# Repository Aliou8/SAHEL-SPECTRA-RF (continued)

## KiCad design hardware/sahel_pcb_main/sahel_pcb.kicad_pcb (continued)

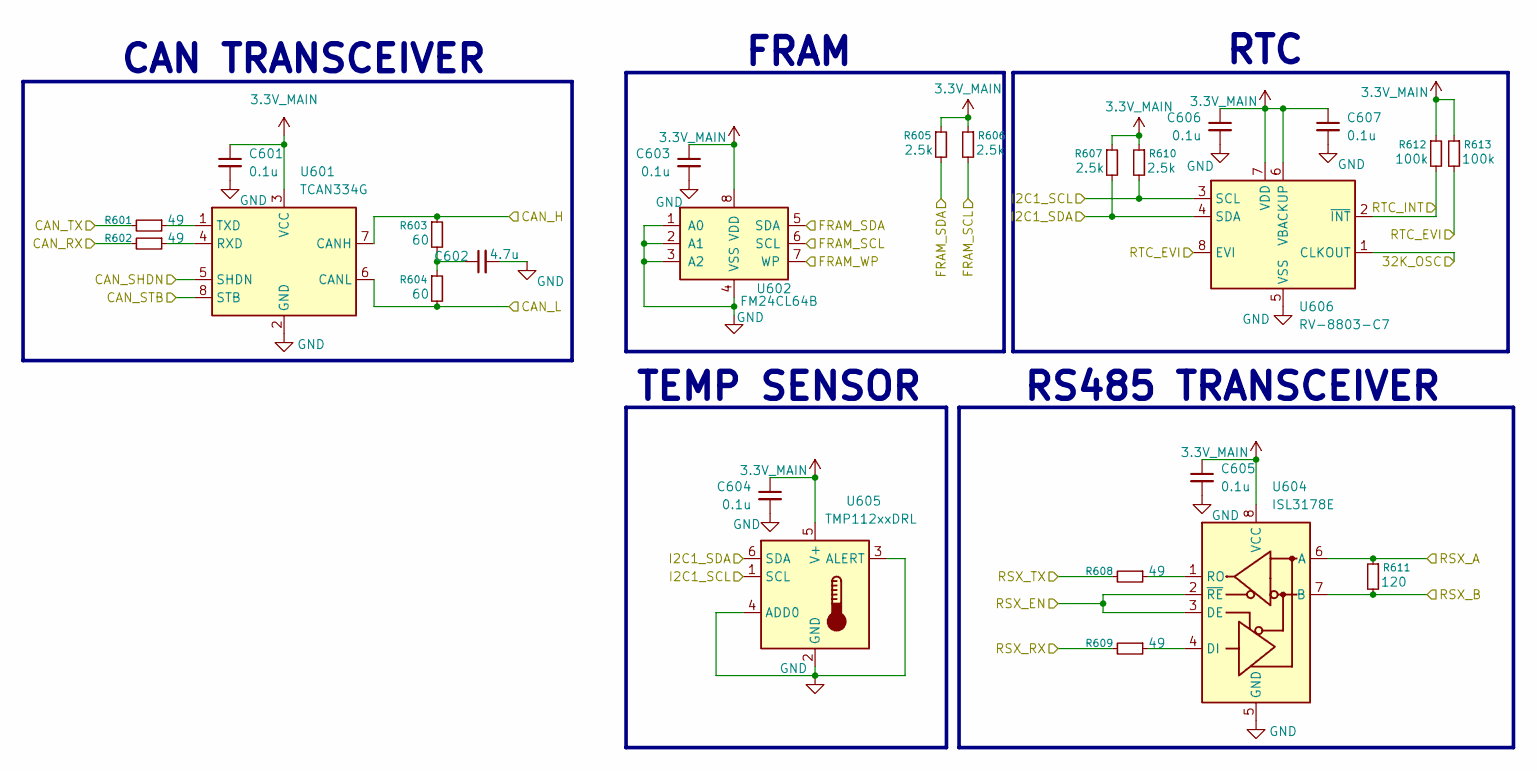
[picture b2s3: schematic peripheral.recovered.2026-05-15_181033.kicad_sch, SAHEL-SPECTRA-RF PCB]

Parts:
C601, C603, C604, C605, C606, C607: 0.1u; C_0402_1005Metric
C602: 4.7u; C_0402_1005Metric
R601, R602, R608, R609: 49; R_0402_1005Metric
R603, R604: 60; R_0402_1005Metric
R605, R606, R607, R610: 2.5k; R_0402_1005Metric
R611: 120; R_0402_1005Metric
R612, R613: 100k; R_0402_1005Metric
U601: TCAN334G; TSOT-23-8
U602: FM24CL64B; SOIC-8_3.9x4.9mm_P1.27mm
U604: ISL3178E; SOIC-8_3.9x4.9mm_P1.27mm
U605: TMP112xxDRL; SOT-563
U606: RV-8803-C7; MicroCrystal_C7_SON-8_1.5x3.2mm_P0.9mm

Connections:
3.3V_MAIN: C601.1, C603.1, C604.1, C605.1, C606.1, C607.1, R605.1, R606.1, R607.1, R610.1, R612.1, R613.1, U601.3 (VCC), U602.8 (VDD), U604.8 (VCC), U605.5 (V+), U606.6 (VBACKUP), U606.7 (VDD); also elsewhere on the board
/BUS_RS_A: R611.1, U604.6 (A); also elsewhere on the board
/BUS_RS_B: R611.2, U604.7 (B); also elsewhere on the board
/CAN_H: R603.1, U601.7 (CANH); also elsewhere on the board
/CAN_L: R604.2, U601.6 (CANL); also elsewhere on the board
/MCU/FDCAN1_RX: R602.2; also elsewhere on the board
/MCU/FDCAN1_TX: R601.2; also elsewhere on the board
/MCU/I2C3_SCL: R606.2, U602.6 (SCL); also elsewhere on the board
/MCU/I2C3_SDA: R605.2, U602.5 (SDA); also elsewhere on the board
/MCU/OSC32_IN: U606.1 (CLKOUT); also elsewhere on the board
/MCU/PA15: U601.5 (SHDN); also elsewhere on the board
/MCU/PB4: R613.2, U606.8 (EVI); also elsewhere on the board
/MCU/PB5: R612.2, U606.2 (~INT); also elsewhere on the board
/MCU/PC6: U602.7 (WP); also elsewhere on the board
/MCU/PD2: U601.8 (STB); also elsewhere on the board
/MCU/USART2_DE: U604.2 (~RE), U604.3 (DE); also elsewhere on the board
/MCU/USART2_RX: R609.2; also elsewhere on the board
/MCU/USART2_TX: R608.2; also elsewhere on the board
/_SCL: R610.2, U605.1 (SCL), U606.3 (SCL); also elsewhere on the board
/_SDA: R607.2, U605.6 (SDA), U606.4 (SDA); also elsewhere on the board
GND: C601.2, C602.2, C603.2, C604.2, C605.2, C606.2, C607.2, U601.2 (GND), U602.1 (A0), U602.2 (A1), U602.3 (A2), U602.4 (VSS), U604.5 (GND), U605.2 (GND), U605.3 (ALERT), U605.4 (ADD0), U606.5 (VSS); also elsewhere on the board
unnamed: C602.1, R603.2, R604.1
unnamed: R602.1, U601.4 (RXD)
unnamed: R601.1, U601.1 (TXD)
unnamed: R609.1, U604.4 (DI)
unnamed: R608.1, U604.1 (RO)

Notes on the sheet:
RTC
CAN TRANSCEIVER
RS485 TRANSCEIVER
TEMP SENSOR
FRAM

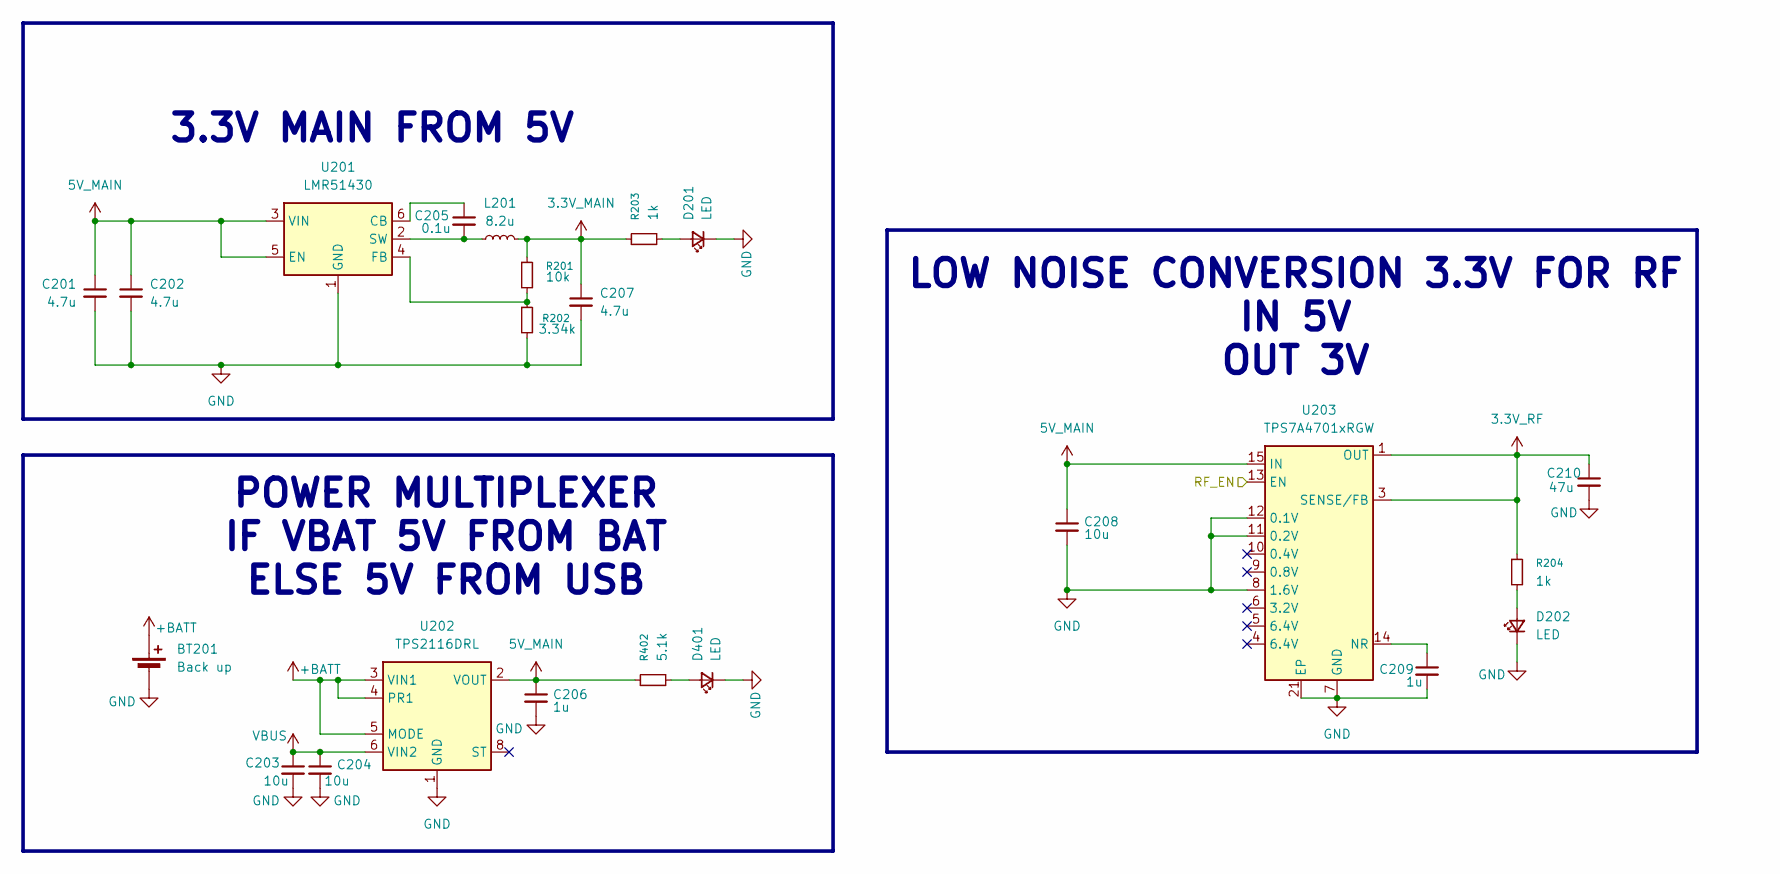
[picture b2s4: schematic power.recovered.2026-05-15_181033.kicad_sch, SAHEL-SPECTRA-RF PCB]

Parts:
BT201: Back up; JST_XH_S2B-XH-A_1x02_P2.50mm_Horizontal
C201, C202, C207: 4.7u; C_0603_1608Metric
C203, C204, C208: 10u; C_0402_1005Metric
C205: 0.1u; C_0402_1005Metric
C206, C209: 1u; C_0402_1005Metric
C210: 47u; C_0402_1005Metric
D201, D202, D401: LED; LED_0402_1005Metric
L201: 8.2u; L_Wurth_WE-LQSH-2010
R201: 10k; R_0402_1005Metric
R202: 3.34k; R_0402_1005Metric
R203, R204: 1k; R_0402_1005Metric
R402: 5.1k; R_0402_1005Metric
U201: LMR51430; SOT-23-6
U202: TPS2116DRL; SOT-583-8
U203: TPS7A4701xRGW; Texas_RGW0020A_VQFN-20-1EP_5x5mm_P0.65mm_EP3.15x3.15mm_Ther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

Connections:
3.3V_MAIN: C207.1, L201.2, R201.1, R203.1; also elsewhere on the board
3.3V_RF: C210.1, R204.1, U203.1 (OUT), U203.3 (SENSE/FB), U203.20 (OUT); also elsewhere on the board
5V_MAIN: C201.1, C202.1, C206.1, C208.1, R402.1, U201.3 (VIN), U201.5 (EN), U202.2 (VOUT), U202.7 (VOUT), U203.15 (IN), U203.16 (IN)
+BATT: BT201.1 (+), U202.3 (VIN1), U202.4 (PR1), U202.5 (MODE)
/MCU/PA0: U203.13 (EN); also elsewhere on the board
GND: BT201.2 (-), C201.2, C202.2, C203.2, C204.2, C206.2, C207.2, C208.2, C209.2, C210.2, D201.1 (K), D202.1 (K), D401.1 (K), R202.2, U201.1 (GND), U202.1 (GND), U203.7 (GND), U203.8 (1.6V), U203.11 (0.2V), U203.12 (0.1V), U203.21 (EP); also elsewhere on the board
unnamed: D201.2 (A), R203.2
unnamed: D202.2 (A), R204.2
unnamed: D401.2 (A), R402.2
unnamed: C205.1, U201.6 (CB)
unnamed: R201.2, R202.1, U201.4 (FB)
unnamed: C205.2, L201.1, U201.2 (SW)
unnamed: C209.1, U203.14 (NR)
VBUS: C203.1, C204.1, U202.6 (VIN2); also elsewhere on the board

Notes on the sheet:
POWER MULTIPLEXER IF VBAT 5V FROM BAT ELSE 5V FROM USB
LOW NOISE CONVERSION 3.3V FOR RF IN 5V OUT 3V
3.3V MAIN FROM 5V

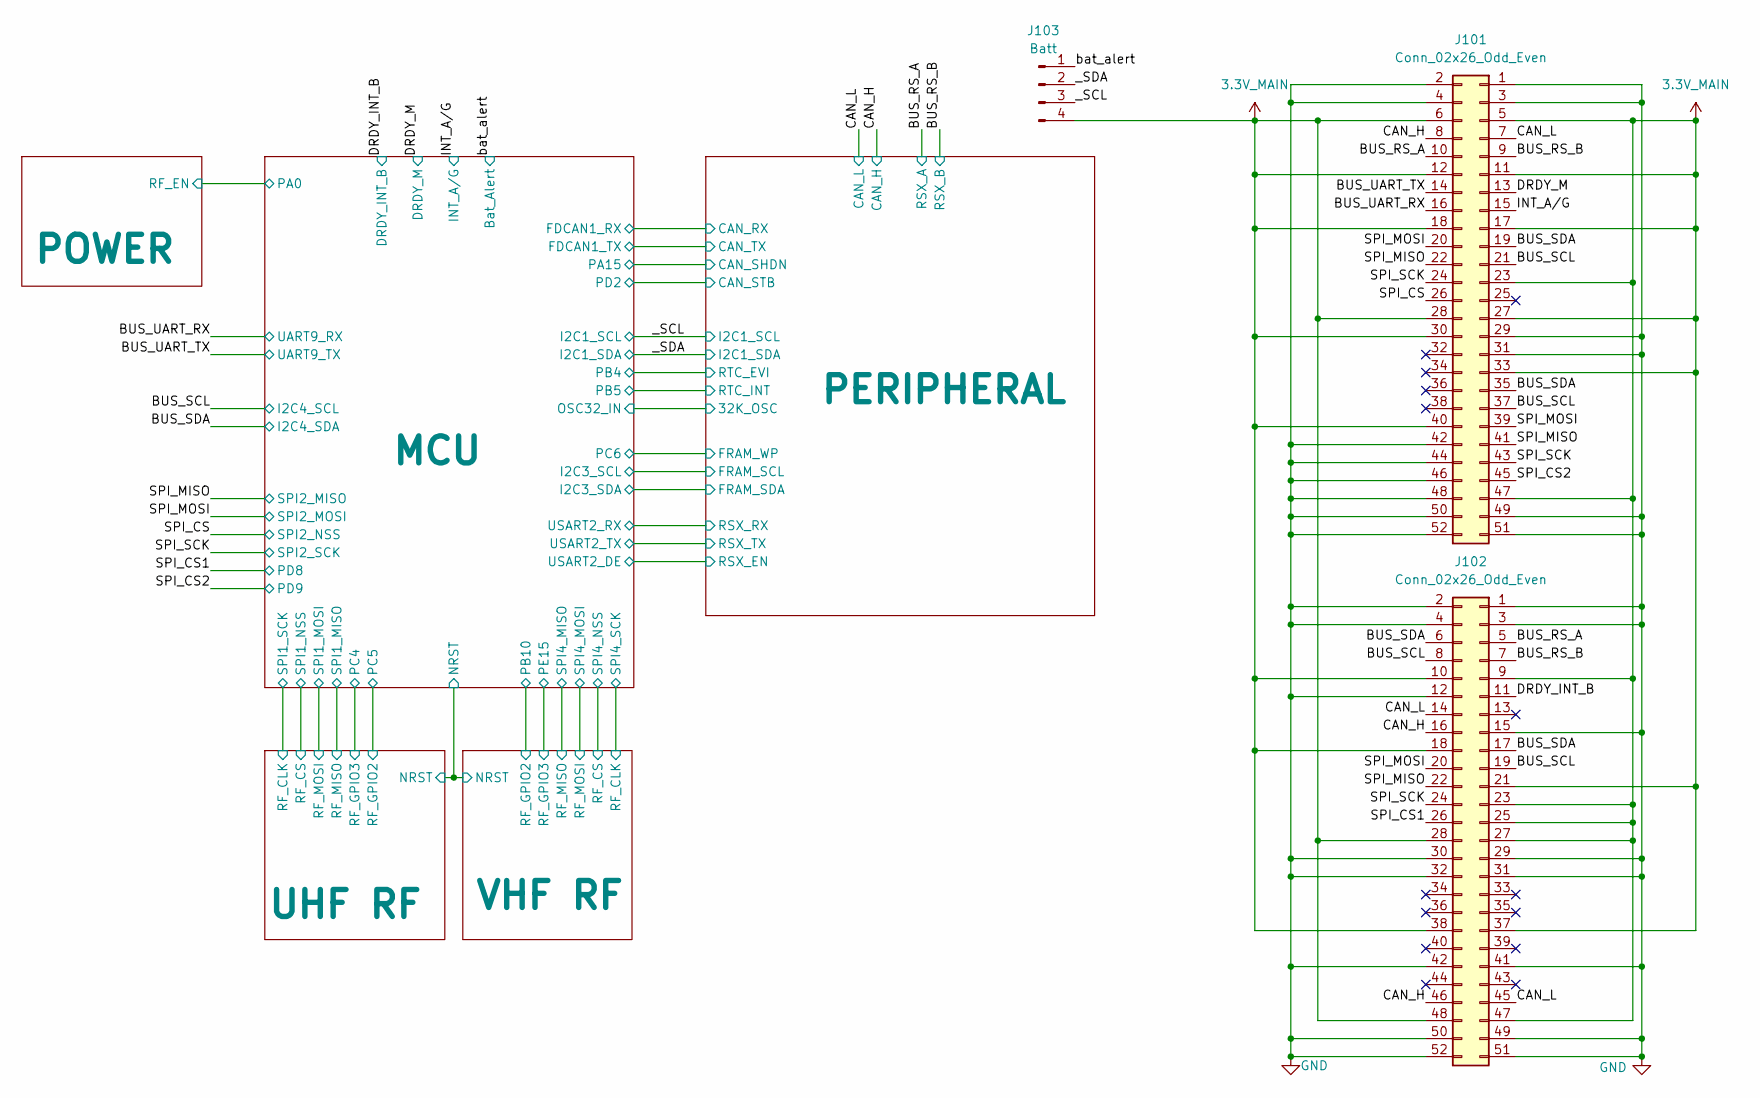
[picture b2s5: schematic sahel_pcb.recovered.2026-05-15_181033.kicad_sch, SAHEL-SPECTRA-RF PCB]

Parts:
J101, J102: Conn_02x26_Odd_Even; PinSocket_2x26_P2.54mm_Vertical
J103: Batt; JST_ZH_B4B-ZR_1x04_P1.50mm_Vertical

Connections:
3.3V_MAIN: J101.5, J101.6, J101.11, J101.12, J101.17, J101.18, J101.23, J101.27, J101.28, J101.30, J101.33, J101.40, J101.47, J102.9, J102.10, J102.18, J102.21, J102.23, J102.25, J102.27, J102.28, J102.37, J102.38, J102.47, J102.48, J103.4; also elsewhere on the board
/BUS_RS_A: J101.10, J102.5; also elsewhere on the board
/BUS_RS_B: J101.9, J102.7; also elsewhere on the board
/BUS_SCL: J101.21, J101.37, J102.8, J102.19; also elsewhere on the board
/BUS_SDA: J101.19, J101.35, J102.6, J102.17; also elsewhere on the board
/BUS_UART_RX: J101.16; also elsewhere on the board
/BUS_UART_TX: J101.14; also elsewhere on the board
/CAN_H: J101.8, J102.16, J102.46; also elsewhere on the board
/CAN_L: J101.7, J102.14, J102.45; also elsewhere on the board
/DRDY_INT_B: J102.11; also elsewhere on the board
/DRDY_M: J101.13; also elsewhere on the board
/INT_A/G: J101.15; also elsewhere on the board
/SPI_CS: J101.26; also elsewhere on the board
/SPI_CS1: J102.26; also elsewhere on the board
/SPI_CS2: J101.45; also elsewhere on the board
/SPI_MISO: J101.22, J101.41, J102.22; also elsewhere on the board
/SPI_MOSI: J101.20, J101.39, J102.20; also elsewhere on the board
/SPI_SCK: J101.24, J101.43, J102.24; also elsewhere on the board
/_SCL: J103.3; also elsewhere on the board
/_SDA: J103.2; also elsewhere on the board
/bat_alert: J103.1; also elsewhere on the board
GND: J101.1, J101.2, J101.3, J101.4, J101.29, J101.31, J101.42, J101.44, J101.46, J101.48, J101.49, J101.50, J101.51, J101.52, J102.1, J102.2, J102.3, J102.4, J102.12, J102.15, J102.29, J102.30, J102.31, J102.32, J102.41, J102.42, J102.49, J102.50, J102.51, J102.52; also elsewhere on the board

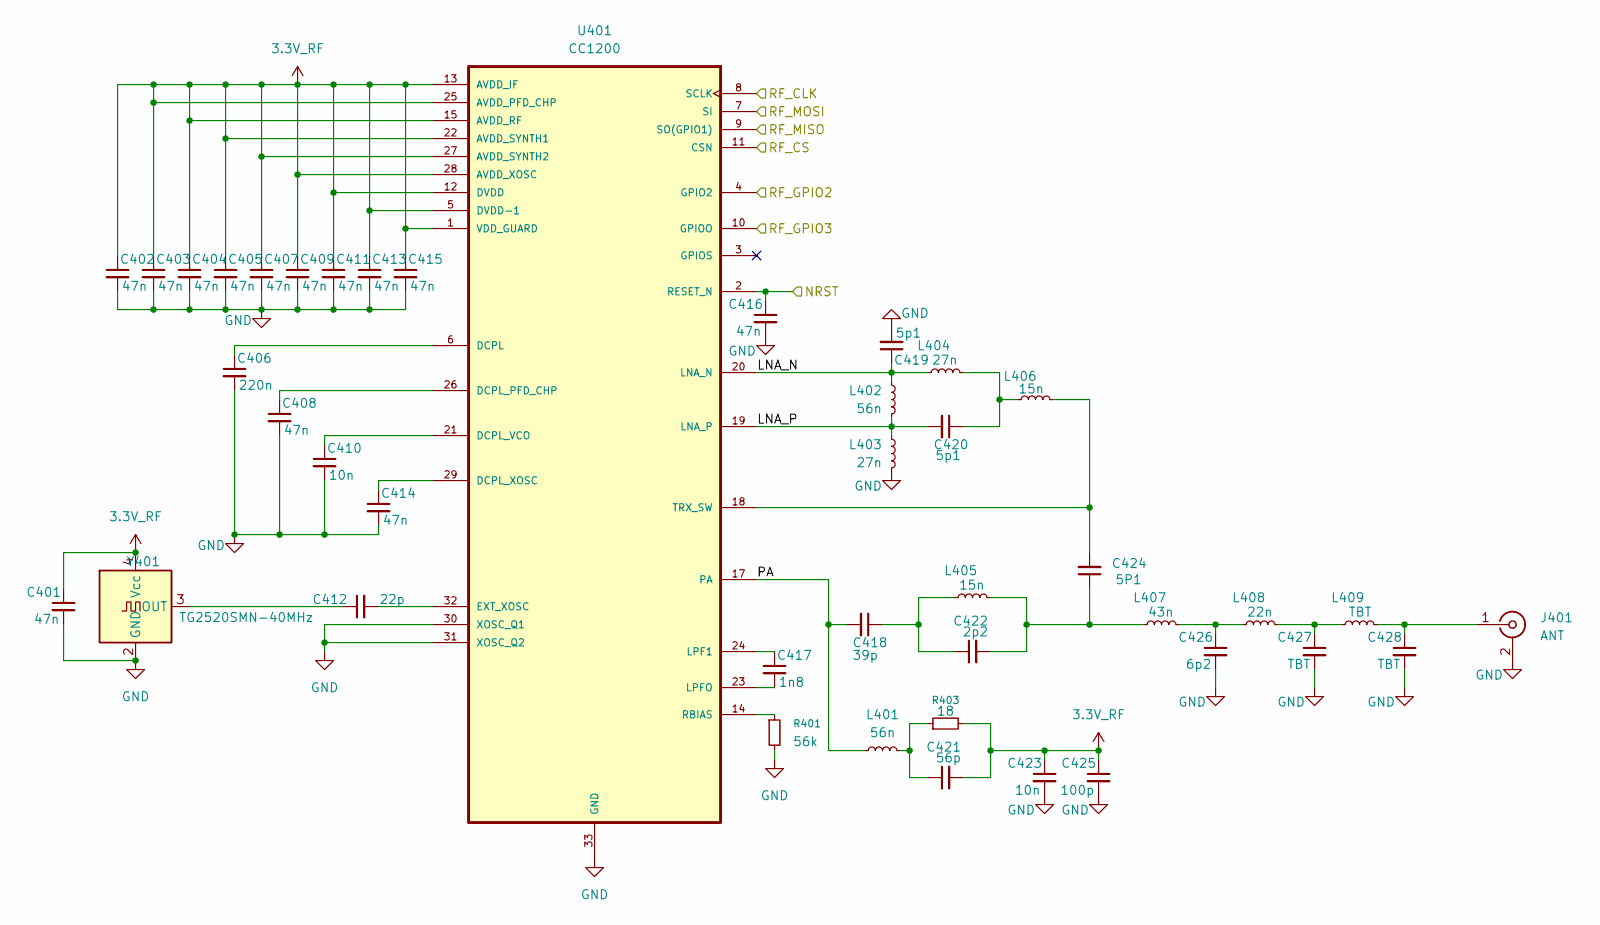
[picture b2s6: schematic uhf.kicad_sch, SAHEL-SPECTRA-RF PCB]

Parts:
C401, C402, C403, C404, C405, C407, C408, C409, C411, C413, C414, C415, C416: 47n; C_0402_1005Metric
C406: 220n; C_0402_1005Metric
C410, C423: 10n; C_0402_1005Metric
C412: 22p; C_0402_1005Metric
C417: 1n8; C_0402_1005Metric
C418: 39p; C_0402_1005Metric
C419, C420: 5p1; C_0402_1005Metric
C421: 56p; C_0402_1005Metric
C422: 2p2; C_0402_1005Metric
C424: 5P1; C_0402_1005Metric
C425: 100p; C_0402_1005Metric
C426: 6p2; C_0402_1005Metric
C427, C428: TBT; C_0402_1005Metric
J401: ANT; U.FL_Hirose_U.FL-R-SMT-1_Vertical
L401, L402: 56n; L_0402_1005Metric
L403, L404: 27n; L_0402_1005Metric
L405, L406: 15n; L_0402_1005Metric
L407: 43n; L_0402_1005Metric
L408: 22n; L_0402_1005Metric
L409: TBT; L_0402_1005Metric
R401: 56k; R_0402_1005Metric
R403: 18; R_0402_1005Metric
U401: CC1200; QFN-32-1EP_5x5mm_P0.5mm_EP3.45x3.45mm
Y401: TG2520SMN-40MHz; Crystal_SMD_WE_CFPX-218-4Pin_2.5x2.0mm

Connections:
3.3V_RF: C401.1, C402.1, C403.1, C404.1, C405.1, C407.1, C409.1, C411.1, C413.1, C415.1, C421.2, C423.1, C425.1, R403.2, U401.1 (VDD_GUARD), U401.5 (DVDD-1), U401.12 (DVDD), U401.13 (AVDD_IF), U401.15 (AVDD_RF), U401.22 (AVDD_SYNTH1), U401.25 (AVDD_PFD_CHP), U401.27 (AVDD_SYNTH2), U401.28 (AVDD_XOSC), Y401.4 (Vcc); also elsewhere on the board
/MCU/NRST: C416.1, U401.2 (RESET_N); also elsewhere on the board
/MCU/PC4: U401.10 (GPIOO); also elsewhere on the board
/MCU/PC5: U401.4 (GPIO2); also elsewhere on the board
/MCU/SPI1_MISO: U401.9 (SO(GPIO1)); also elsewhere on the board
/MCU/SPI1_MOSI: U401.7 (SI); also elsewhere on the board
/MCU/SPI1_NSS: U401.11 (CSN); also elsewhere on the board
/MCU/SPI1_SCK: U401.8 (SCLK); also elsewhere on the board
/UHF RF/LNA_N: C419.1, L402.2, L404.2, U401.20 (LNA_N)
/UHF RF/LNA_P: C420.2, L402.1, L403.2, U401.19 (LNA_P)
/UHF RF/PA: C418.2, L401.1, U401.17 (PA)
GND: C401.2, C402.2, C403.2, C404.2, C405.2, C406.2, C407.2, C408.2, C409.2, C410.2, C411.2, C413.2, C414.2, C415.2, C416.2, C419.2, C423.2, C425.2, C426.2, C427.2, C428.2, J401.2 (Ext), L403.1, R401.2, U401.30 (XOSC_Q1), U401.31 (XOSC_Q2), U401.33 (GND), Y401.2 (GND); also elsewhere on the board
unnamed: C418.1, C422.1, L405.2
unnamed: C420.1, L404.1, L406.2
unnamed: C421.1, L401.2, R403.1
unnamed: C422.2, C424.1, L405.1, L407.2
unnamed: C426.1, L407.1, L408.2
unnamed: C427.1, L408.1, L409.2
unnamed: C428.1, J401.1 (In), L409.1
unnamed: C406.1, U401.6 (DCPL)
unnamed: C408.1, U401.26 (DCPL_PFD_CHP)
unnamed: C410.1, U401.21 (DCPL_VCO)
unnamed: C414.1, U401.29 (DCPL_XOSC)
unnamed: C412.2, U401.32 (EXT_XOSC)
unnamed: C417.1, U401.24 (LPF1)
unnamed: C417.2, U401.23 (LPFO)
unnamed: R401.1, U401.14 (RBIAS)
unnamed: C424.2, L406.1, U401.18 (TRX_SW)
unnamed: C412.1, Y401.3 (OUT)

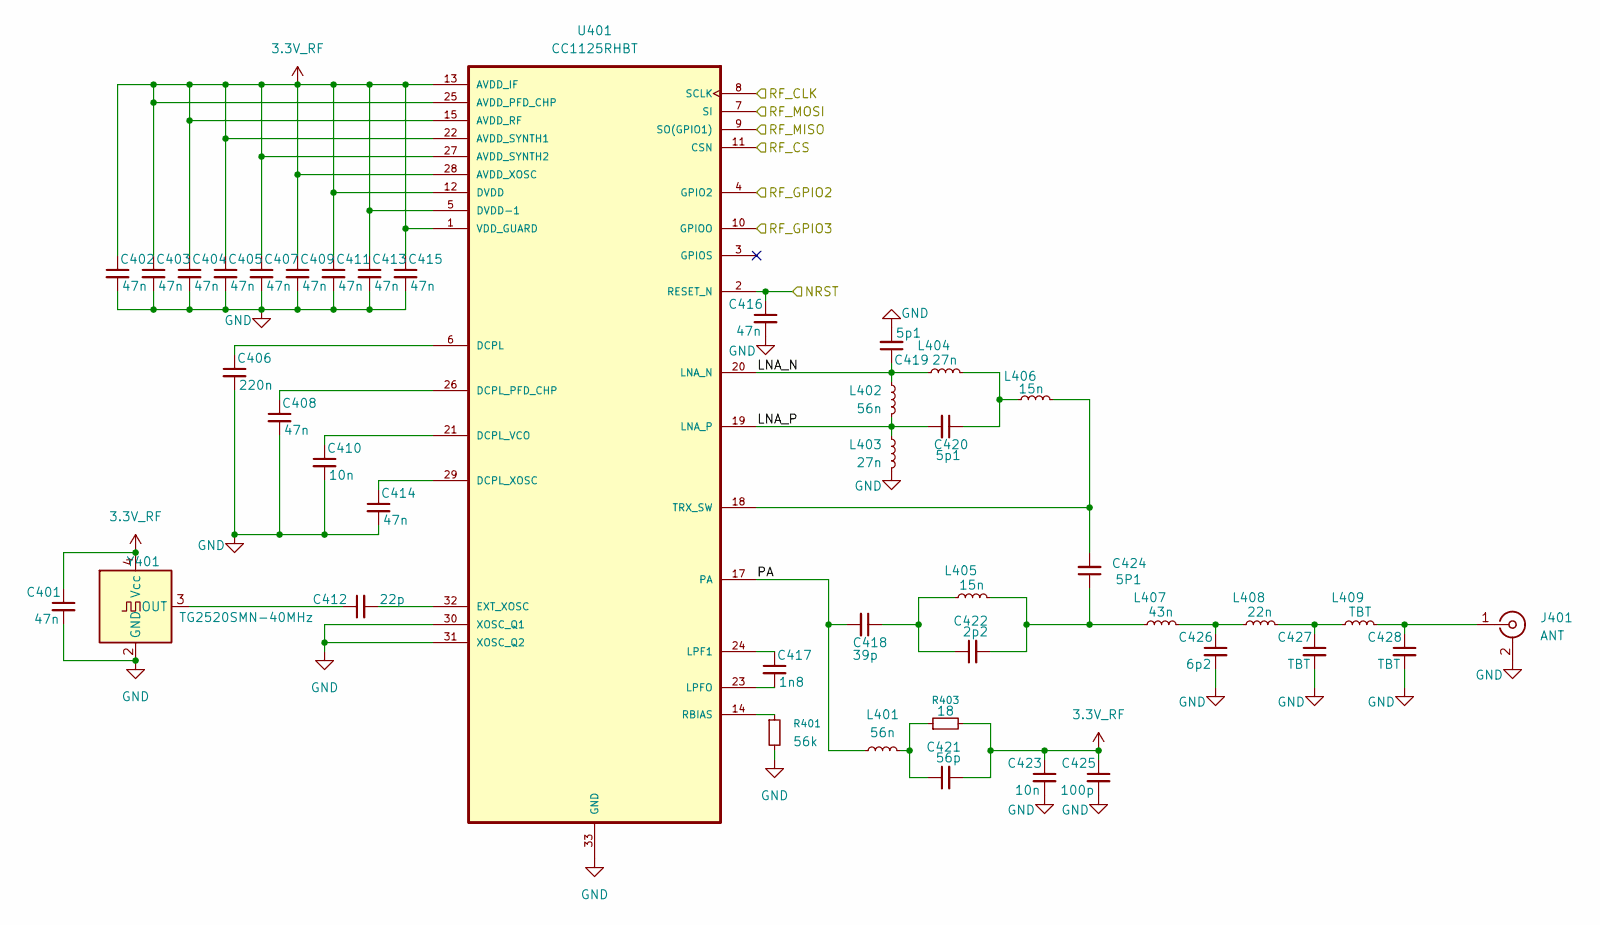
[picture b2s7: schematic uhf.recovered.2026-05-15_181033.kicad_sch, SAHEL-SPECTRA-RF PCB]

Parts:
C401, C402, C403, C404, C405, C407, C408, C409, C411, C413, C414, C415, C416: 47n; C_0402_1005Metric
C406: 220n; C_0402_1005Metric
C410, C423: 10n; C_0402_1005Metric
C412: 22p; C_0402_1005Metric
C417: 1n8; C_0402_1005Metric
C418: 39p; C_0402_1005Metric
C419, C420: 5p1; C_0402_1005Metric
C421: 56p; C_0402_1005Metric
C422: 2p2; C_0402_1005Metric
C424: 5P1; C_0402_1005Metric
C425: 100p; C_0402_1005Metric
C426: 6p2; C_0402_1005Metric
C427, C428: TBT; C_0402_1005Metric
J401: ANT; U.FL_Hirose_U.FL-R-SMT-1_Vertical
L401, L402: 56n; L_0402_1005Metric
L403, L404: 27n; L_0402_1005Metric
L405, L406: 15n; L_0402_1005Metric
L407: 43n; L_0402_1005Metric
L408: 22n; L_0402_1005Metric
L409: TBT; L_0402_1005Metric
R401: 56k; R_0402_1005Metric
R403: 18; R_0402_1005Metric
U401: CC1125RHBT; QFN-32-1EP_5x5mm_P0.5mm_EP3.45x3.45mm
Y401: TG2520SMN-40MHz; Crystal_SMD_WE_CFPX-218-4Pin_2.5x2.0mm

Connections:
3.3V_RF: C401.1, C402.1, C403.1, C404.1, C405.1, C407.1, C409.1, C411.1, C413.1, C415.1, C421.2, C423.1, C425.1, R403.2, U401.1 (VDD_GUARD), U401.5 (DVDD-1), U401.12 (DVDD), U401.13 (AVDD_IF), U401.15 (AVDD_RF), U401.22 (AVDD_SYNTH1), U401.25 (AVDD_PFD_CHP), U401.27 (AVDD_SYNTH2), U401.28 (AVDD_XOSC), Y401.4 (Vcc); also elsewhere on the board
/MCU/NRST: C416.1, U401.2 (RESET_N); also elsewhere on the board
/MCU/PC4: U401.10 (GPIOO); also elsewhere on the board
/MCU/PC5: U401.4 (GPIO2); also elsewhere on the board
/MCU/SPI1_MISO: U401.9 (SO(GPIO1)); also elsewhere on the board
/MCU/SPI1_MOSI: U401.7 (SI); also elsewhere on the board
/MCU/SPI1_NSS: U401.11 (CSN); also elsewhere on the board
/MCU/SPI1_SCK: U401.8 (SCLK); also elsewhere on the board
/UHF RF/LNA_N: C419.1, L402.2, L404.2, U401.20 (LNA_N)
/UHF RF/LNA_P: C420.2, L402.1, L403.2, U401.19 (LNA_P)
/UHF RF/PA: C418.2, L401.1, U401.17 (PA)
GND: C401.2, C402.2, C403.2, C404.2, C405.2, C406.2, C407.2, C408.2, C409.2, C410.2, C411.2, C413.2, C414.2, C415.2, C416.2, C419.2, C423.2, C425.2, C426.2, C427.2, C428.2, J401.2 (Ext), L403.1, R401.2, U401.30 (XOSC_Q1), U401.31 (XOSC_Q2), U401.33 (GND), Y401.2 (GND); also elsewhere on the board
unnamed: C418.1, C422.1, L405.2
unnamed: C420.1, L404.1, L406.2
unnamed: C421.1, L401.2, R403.1
unnamed: C422.2, C424.1, L405.1, L407.2
unnamed: C426.1, L407.1, L408.2
unnamed: C427.1, L408.1, L409.2
unnamed: C428.1, J401.1 (In), L409.1
unnamed: C406.1, U401.6 (DCPL)
unnamed: C408.1, U401.26 (DCPL_PFD_CHP)
unnamed: C410.1, U401.21 (DCPL_VCO)
unnamed: C414.1, U401.29 (DCPL_XOSC)
unnamed: C412.2, U401.32 (EXT_XOSC)
unnamed: C417.1, U401.24 (LPF1)
unnamed: C417.2, U401.23 (LPFO)
unnamed: R401.1, U401.14 (RBIAS)
unnamed: C424.2, L406.1, U401.18 (TRX_SW)
unnamed: C412.1, Y401.3 (OUT)

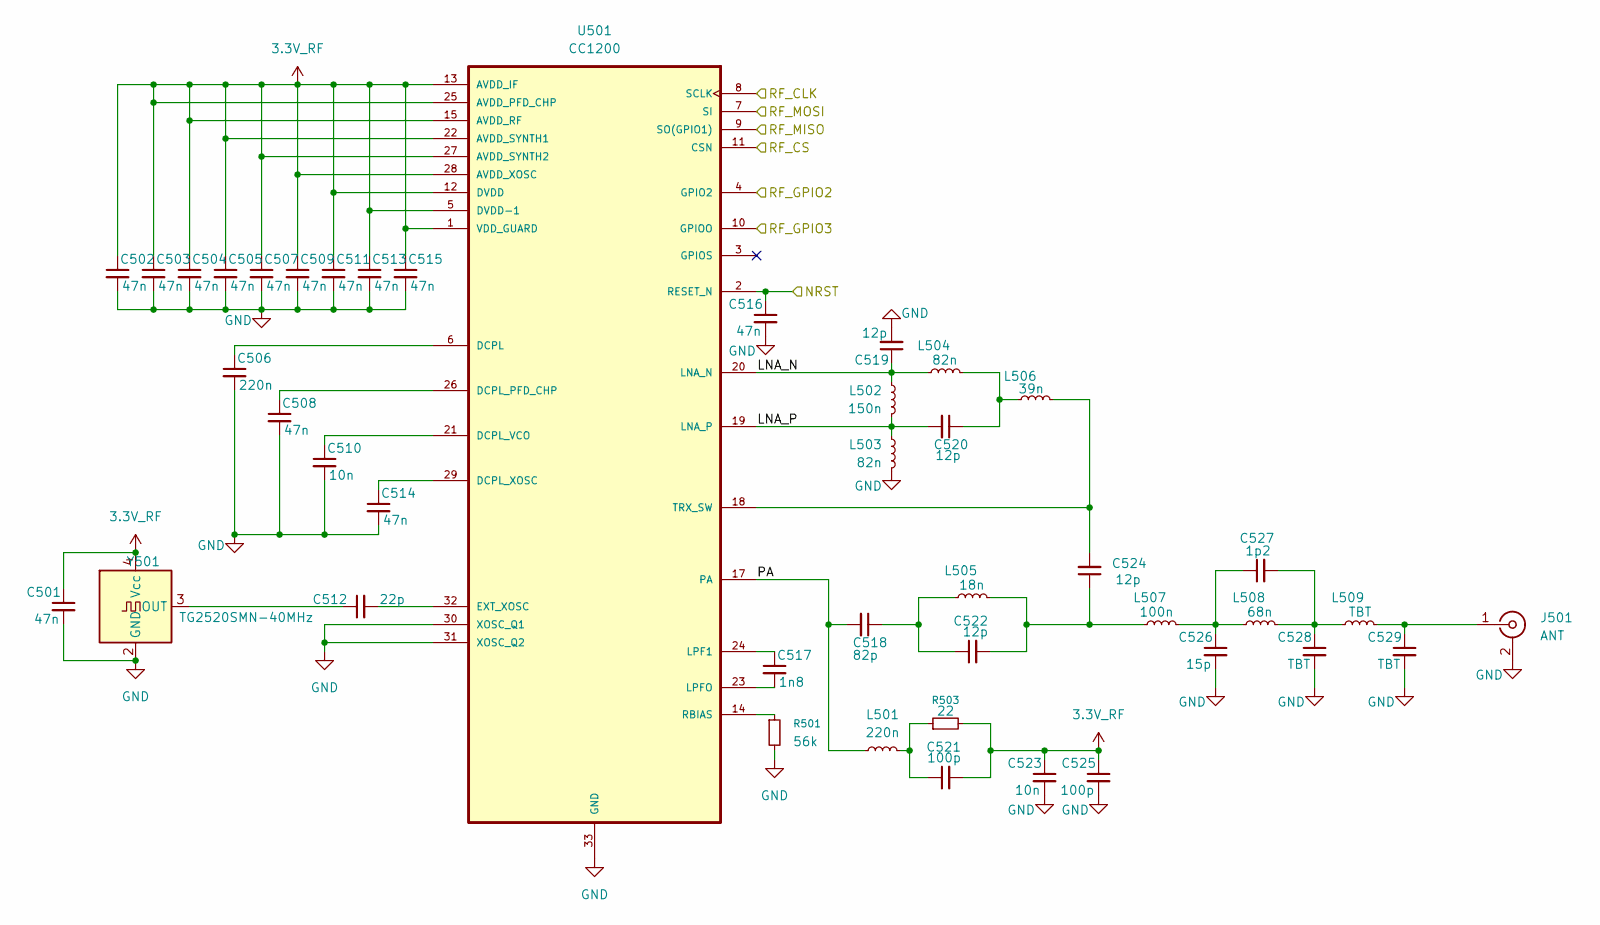
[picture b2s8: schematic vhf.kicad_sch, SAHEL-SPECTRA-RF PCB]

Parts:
C501, C502, C503, C504, C505, C507, C508, C509, C511, C513, C514, C515, C516: 47n; C_0402_1005Metric
C506: 220n; C_0402_1005Metric
C510, C523: 10n; C_0402_1005Metric
C512: 22p; C_0402_1005Metric
C517: 1n8; C_0402_1005Metric
C518: 82p; C_0402_1005Metric
C519, C520, C522, C524: 12p; C_0402_1005Metric
C521, C525: 100p; C_0402_1005Metric
C526: 15p; C_0402_1005Metric
C527: 1p2; C_0402_1005Metric
C528, C529: TBT; C_0402_1005Metric
J501: ANT; U.FL_Hirose_U.FL-R-SMT-1_Vertical
L501: 220n; L_0402_1005Metric
L502: 150n; L_0402_1005Metric
L503, L504: 82n; L_0402_1005Metric
L505: 18n; L_0402_1005Metric
L506: 39n; L_0402_1005Metric
L507: 100n; L_0402_1005Metric
L508: 68n; L_0402_1005Metric
L509: TBT; L_0402_1005Metric
R501: 56k; R_0402_1005Metric
R503: 22; R_0402_1005Metric
U501: CC1200; QFN-32-1EP_5x5mm_P0.5mm_EP3.45x3.45mm
Y501: TG2520SMN-40MHz; Crystal_SMD_WE_CFPX-218-4Pin_2.5x2.0mm

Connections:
3.3V_RF: C501.1, C502.1, C503.1, C504.1, C505.1, C507.1, C509.1, C511.1, C513.1, C515.1, C521.2, C523.1, C525.1, R503.2, U501.1 (VDD_GUARD), U501.5 (DVDD-1), U501.12 (DVDD), U501.13 (AVDD_IF), U501.15 (AVDD_RF), U501.22 (AVDD_SYNTH1), U501.25 (AVDD_PFD_CHP), U501.27 (AVDD_SYNTH2), U501.28 (AVDD_XOSC), Y501.4 (Vcc); also elsewhere on the board
/MCU/NRST: C516.1, U501.2 (RESET_N); also elsewhere on the board
/MCU/PB10: U501.4 (GPIO2); also elsewhere on the board
/MCU/PE15: U501.10 (GPIOO); also elsewhere on the board
/MCU/SPI4_MISO: U501.9 (SO(GPIO1)); also elsewhere on the board
/MCU/SPI4_MOSI: U501.7 (SI); also elsewhere on the board
/MCU/SPI4_NSS: U501.11 (CSN); also elsewhere on the board
/MCU/SPI4_SCK: U501.8 (SCLK); also elsewhere on the board
/VHF RF/LNA_N: C519.1, L502.2, L504.2, U501.20 (LNA_N)
/VHF RF/LNA_P: C520.2, L502.1, L503.2, U501.19 (LNA_P)
/VHF RF/PA: C518.2, L501.1, U501.17 (PA)
GND: C501.2, C502.2, C503.2, C504.2, C505.2, C506.2, C507.2, C508.2, C509.2, C510.2, C511.2, C513.2, C514.2, C515.2, C516.2, C519.2, C523.2, C525.2, C526.2, C528.2, C529.2, J501.2 (Ext), L503.1, R501.2, U501.30 (XOSC_Q1), U501.31 (XOSC_Q2), U501.33 (GND), Y501.2 (GND); also elsewhere on the board
unnamed: C518.1, C522.1, L505.2
unnamed: C520.1, L504.1, L506.2
unnamed: C521.1, L501.2, R503.1
unnamed: C522.2, C524.1, L505.1, L507.2
unnamed: C526.1, C527.1, L507.1, L508.2
unnamed: C527.2, C528.1, L508.1, L509.2
unnamed: C529.1, J501.1 (In), L509.1
unnamed: C506.1, U501.6 (DCPL)
unnamed: C508.1, U501.26 (DCPL_PFD_CHP)
unnamed: C510.1, U501.21 (DCPL_VCO)
unnamed: C514.1, U501.29 (DCPL_XOSC)
unnamed: C512.2, U501.32 (EXT_XOSC)
unnamed: C517.1, U501.24 (LPF1)
unnamed: C517.2, U501.23 (LPFO)
unnamed: R501.1, U501.14 (RBIAS)
unnamed: C524.2, L506.1, U501.18 (TRX_SW)
unnamed: C512.1, Y501.3 (OUT)

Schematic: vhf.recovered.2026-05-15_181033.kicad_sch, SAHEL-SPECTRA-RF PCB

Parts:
C501, C502, C503, C504, C505, C507, C508, C509, C511, C513, C514, C515, C516: 47n; C_0402_1005Metric
C506: 220n; C_0402_1005Metric
C510, C523: 10n; C_0402_1005Metric
C512: 22p; C_0402_1005Metric
C517: 1n8; C_0402_1005Metric
C518: 82p; C_0402_1005Metric
C519, C520, C522, C524: 12p; C_0402_1005Metric
C521, C525: 100p; C_0402_1005Metric
C526: 15p; C_0402_1005Metric
C527: 1p2; C_0402_1005Metric
C528, C529: TBT; C_0402_1005Metric
J501: ANT; U.FL_Hirose_U.FL-R-SMT-1_Vertical
L501: 220n; L_0402_1005Metric
L502: 150n; L_0402_1005Metric
L503, L504: 82n; L_0402_1005Metric
L505: 18n; L_0402_1005Metric
L506: 39n; L_0402_1005Metric
L507: 100n; L_0402_1005Metric
L508: 68n; L_0402_1005Metric
L509: TBT; L_0402_1005Metric
R501: 56k; R_0402_1005Metric
R503: 22; R_0402_1005Metric
U501: CC1125RHBT; QFN-32-1EP_5x5mm_P0.5mm_EP3.45x3.45mm
Y501: TG2520SMN-40MHz; Crystal_SMD_WE_CFPX-218-4Pin_2.5x2.0mm

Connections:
3.3V_RF: C501.1, C502.1, C503.1, C504.1, C505.1, C507.1, C509.1, C511.1, C513.1, C515.1, C521.2, C523.1, C525.1, R503.2, U501.1 (VDD_GUARD), U501.5 (DVDD-1), U501.12 (DVDD), U501.13 (AVDD_IF), U501.15 (AVDD_RF), U501.22 (AVDD_SYNTH1), U501.25 (AVDD_PFD_CHP), U501.27 (AVDD_SYNTH2), U501.28 (AVDD_XOSC), Y501.4 (Vcc); also elsewhere on the board
/MCU/NRST: C516.1, U501.2 (RESET_N); also elsewhere on the board
/MCU/PB10: U501.4 (GPIO2); also elsewhere on the board
/MCU/PE15: U501.10 (GPIOO); also elsewhere on the board
/MCU/SPI4_MISO: U501.9 (SO(GPIO1)); also elsewhere on the board
/MCU/SPI4_MOSI: U501.7 (SI); also elsewhere on the board
/MCU/SPI4_NSS: U501.11 (CSN); also elsewhere on the board
/MCU/SPI4_SCK: U501.8 (SCLK); also elsewhere on the board
/VHF RF/LNA_N: C519.1, L502.2, L504.2, U501.20 (LNA_N)
/VHF RF/LNA_P: C520.2, L502.1, L503.2, U501.19 (LNA_P)
/VHF RF/PA: C518.2, L501.1, U501.17 (PA)
GND: C501.2, C502.2, C503.2, C504.2, C505.2, C506.2, C507.2, C508.2, C509.2, C510.2, C511.2, C513.2, C514.2, C515.2, C516.2, C519.2, C523.2, C525.2, C526.2, C528.2, C529.2, J501.2 (Ext), L503.1, R501.2, U501.30 (XOSC_Q1), U501.31 (XOSC_Q2), U501.33 (GND), Y501.2 (GND); also elsewhere on the board
unnamed: C518.1, C522.1, L505.2
unnamed: C520.1, L504.1, L506.2
unnamed: C521.1, L501.2, R503.1
unnamed: C522.2, C524.1, L505.1, L507.2
unnamed: C526.1, C527.1, L507.1, L508.2
unnamed: C527.2, C528.1, L508.1, L509.2
unnamed: C529.1, J501.1 (In), L509.1
unnamed: C506.1, U501.6 (DCPL)
unnamed: C508.1, U501.26 (DCPL_PFD_CHP)
unnamed: C510.1, U501.21 (DCPL_VCO)
unnamed: C514.1, U501.29 (DCPL_XOSC)
unnamed: C512.2, U501.32 (EXT_XOSC)
unnamed: C517.1, U501.24 (LPF1)
unnamed: C517.2, U501.23 (LPFO)
unnamed: R501.1, U501.14 (RBIAS)
unnamed: C524.2, L506.1, U501.18 (TRX_SW)
unnamed: C512.1, Y501.3 (OUT)

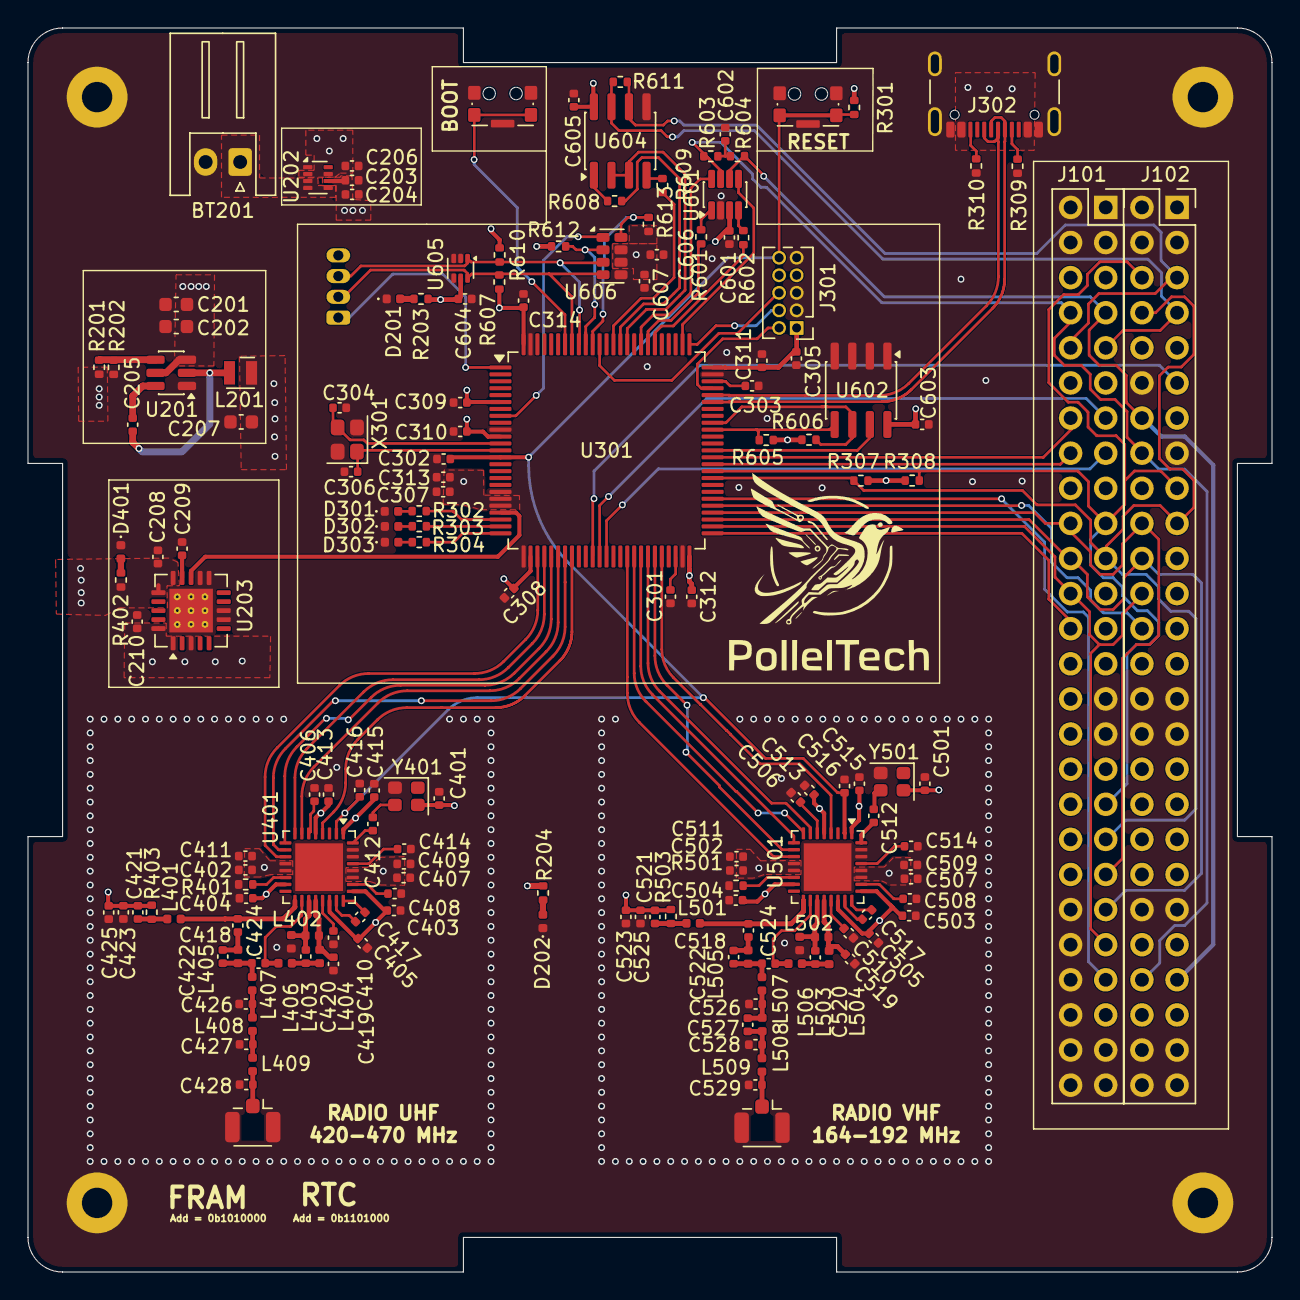
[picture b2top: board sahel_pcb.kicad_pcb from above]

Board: 4 copper layers, 90.0 x 90.0 mm, 171 parts (1 on the bottom side), 123 nets.
